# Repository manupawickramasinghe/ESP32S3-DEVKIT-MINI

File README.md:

# ESP32S3-DEVKIT-MINI
 ESP32-S3 DevKIT Made using the Espressif Schematics, Needs more changes and improvements , donot hesitate to make changes and suggest improvements. Final Plan is to implemnt a global datalogger

 It has Mini USB , MIcro USB and TYpe C 

To do:
Implement USB
Add seperate i2c and spi as connectors to connect to modules - Check my datalogger project
Add Silkscreen things -  Need to do
Improve routing and make it prettier

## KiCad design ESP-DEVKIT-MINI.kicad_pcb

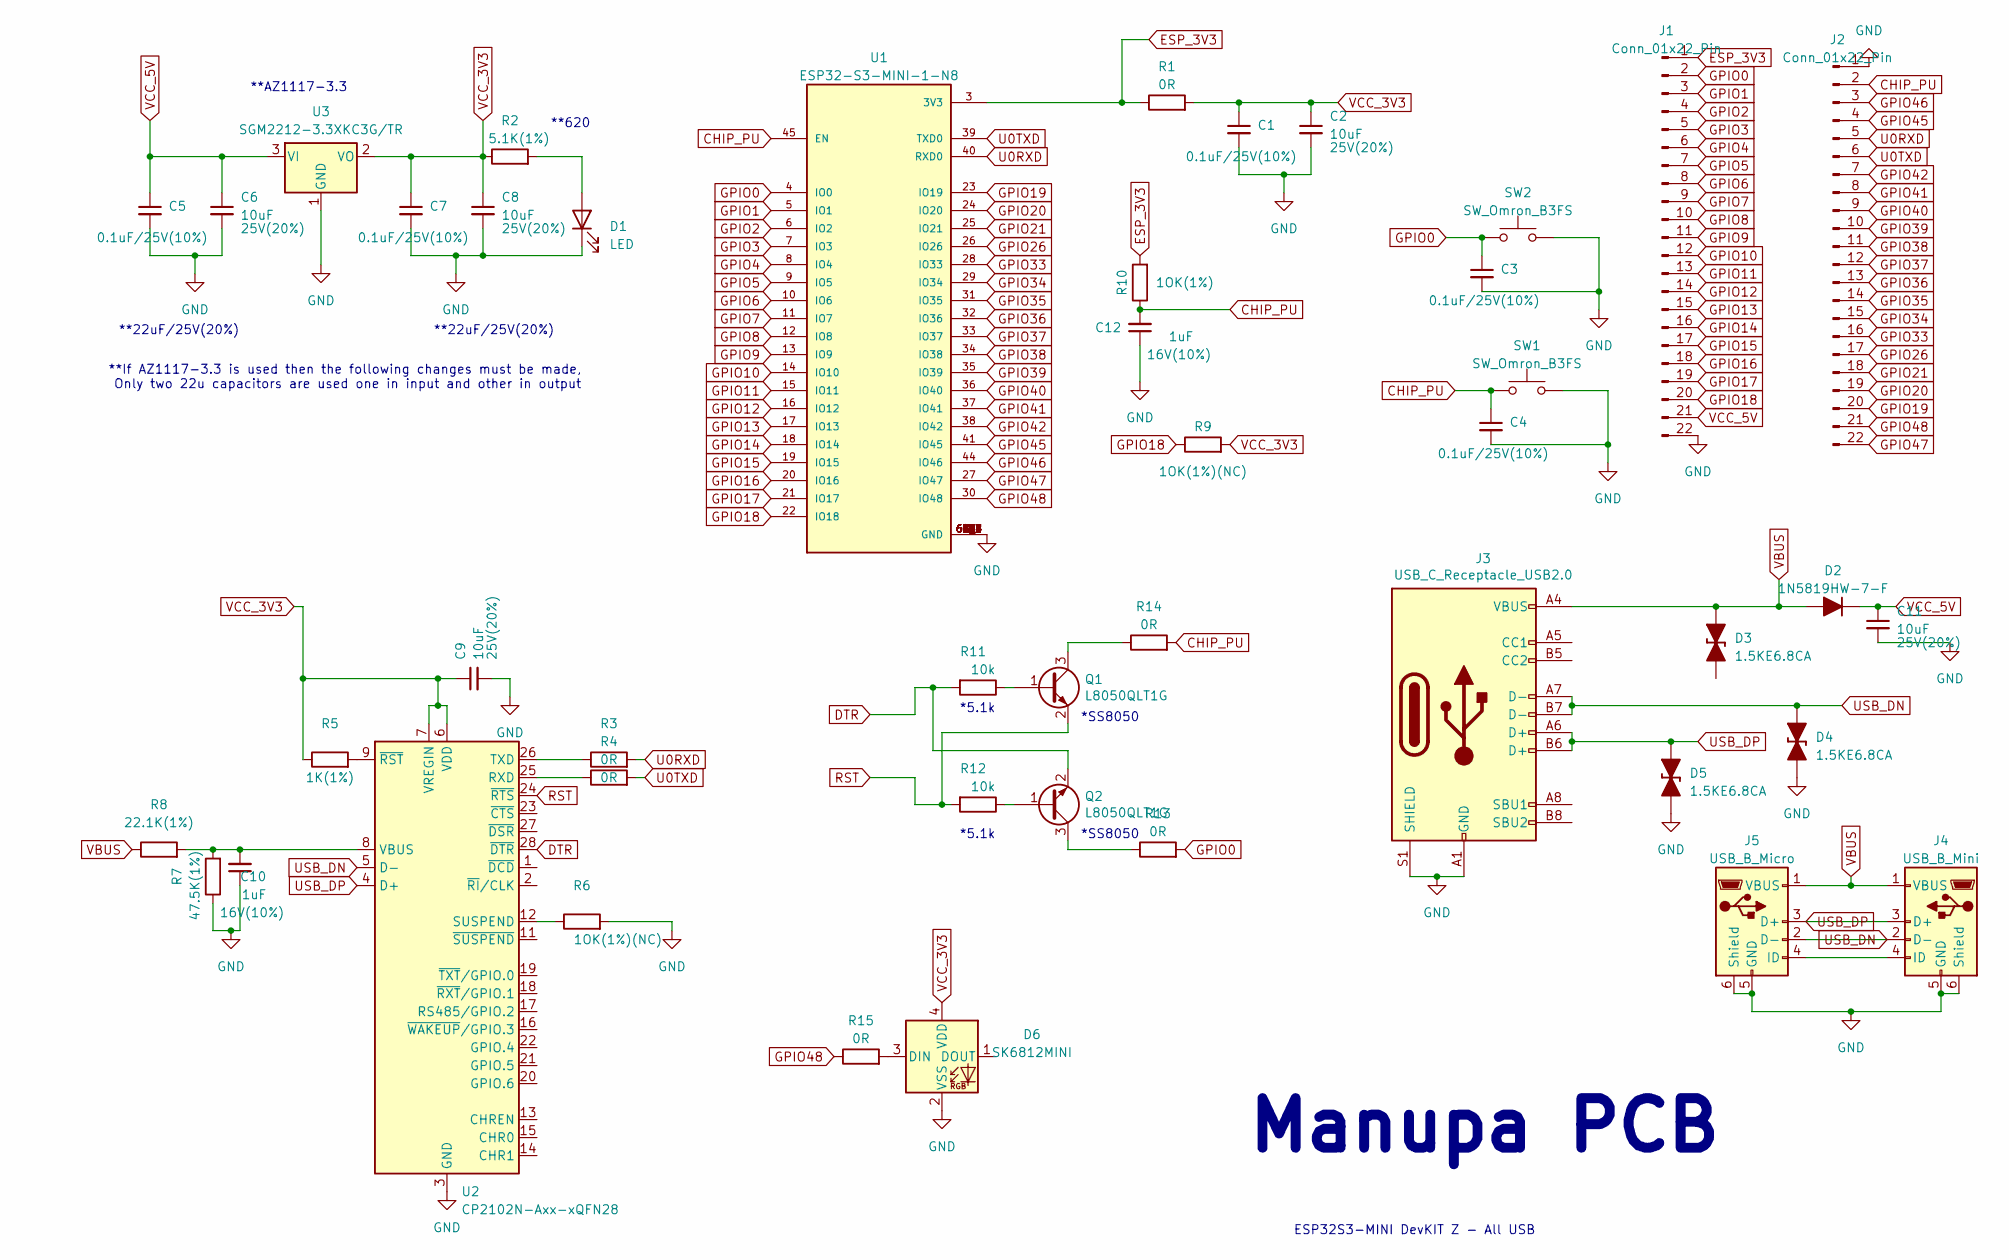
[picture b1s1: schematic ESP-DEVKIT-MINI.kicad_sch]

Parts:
C1, C3, C4, C5, C7: 0.1uF_0603_16V; C_0603_1608Metric; Part Number 0603YC104KAT2A; JLCPCB ID C14663
C2, C6, C8, C9, C11: 10uF_1206_35V; C_0603_1608Metric; Part Number C3216X6S1V106K160AC; JLCPCB ID 25V(20%)
C10, C12: 10uF_1206_35V; C_0603_1608Metric; Part Number C3216X6S1V106K160AC; JLCPCB ID 16V(10%)
D1: LED; LED_0603_1608Metric
D2: 1N5819HW-7-F; D_DO-41_SOD81_P7.62mm_Horizontal
D3, D4, D5: 1.5KE6.8CA; D_DO-201_P12.70mm_Horizontal_TVS
D6: SK6812MINI; LED_SK6812MINI_PLCC4_3.5x3.5mm_P1.75mm
J1, J2: Conn_01x22_Pin; PinHeader_1x22_P2.00mm_Vertical
J3: USB_C_Receptacle_USB2.0; USB_C_Receptacle_Palconn_UTC16-G; LCSC C167321
J4: USB_B_Mini; USB_Mini-B_Lumberg_2486_01_Horizontal
J5: USB_B_Micro; USB_Micro-AB_Molex_47590-0001
Q1, Q2: L8050QLT1G; SOT-23; LCSC C2150
R1, R2, R3, R4, R5, R6, R7, R8, R9, R10, R13, R14, R15: 0R_0603; R_0603; Part Number RC0603FR-100RL; JLCPCB ID C21189
R11, R12: 10k; R_0603; LCSC C25905
SW1, SW2: SW_Omron_B3FS; SW_SPST_Omron_B3FS-100xP
U1: ESP32-S3-MINI-1-N8; XCVR_ESP32-S3-MINI-1-N8; PARTREV v0.6
U2: CP2102N-Axx-xQFN28; QFN-28-1EP_5x5mm_P0.5mm_EP3.35x3.35mm
U3: SGM2212-3.3XKC3G/TR; SOT-223-3_TabPin2

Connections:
CHIP_PU: C4.1, C12.2, J2.2, R10.1, R14.2, SW1.1, U1.45 (EN)
DTR: Q2.2 (E), R11.2, U2.28 (~DTR)
ESP_3V3: J1.1, R1.1, R10.2, U1.3 (3V3)
GND: C1.2, C2.2, C3.2, C4.2, C5.2, C6.2, C7.2, C8.2, C9.2, C10.1, C11.2, C12.1, D1.1 (K), D3.1 (K), D4.1 (K), D5.1 (K), D6.2 (VSS), J1.22, J2.1, J3.A1 (GND), J3.A12 (GND), J3.B1 (GND), J3.B12 (GND), J3.S1 (SHIELD), J4.5 (GND), J4.6 (Shield), J5.5 (GND), J5.6 (Shield), R6.2, R7.1, SW1.2, SW2.2, U1.1 (GND), U1.2 (GND), U1.42 (GND), U1.43 (GND), U1.46 (GND), U1.47 (GND), U1.48 (GND), U1.49 (GND), U1.50 (GND), U1.51 (GND), U1.52 (GND), U1.53 (GND), U1.54 (GND), U1.55 (GND), U1.56 (GND), U1.57 (GND), U1.58 (GND), U1.59 (GND), U1.60 (GND), U1.61 (GND), U1.61_1 (GND), U1.61_2 (GND), U1.61_3 (GND), U1.61_4 (GND), U1.61_5 (GND), U1.61_6 (GND), U1.61_7 (GND), U1.61_8 (GND), U1.62 (GND), U1.63 (GND), U1.64 (GND), U1.65 (GND), U2.3 (GND), U2.29 (GND), U3.1 (GND)
GPIO0: C3.1, J1.2, R13.2, SW2.1, U1.4 (IO0)
GPIO1: J1.3, U1.5 (IO1)
GPIO2: J1.4, U1.6 (IO2)
GPIO3: J1.5, U1.7 (IO3)
GPIO4: J1.6, U1.8 (IO4)
GPIO5: J1.7, U1.9 (IO5)
GPIO6: J1.8, U1.10 (IO6)
GPIO7: J1.9, U1.11 (IO7)
GPIO8: J1.10, U1.12 (IO8)
GPIO9: J1.11, U1.13 (IO9)
GPIO10: J1.12, U1.14 (IO10)
GPIO11: J1.13, U1.15 (IO11)
GPIO12: J1.14, U1.16 (IO12)
GPIO13: J1.15, U1.17 (IO13)
GPIO14: J1.16, U1.18 (IO14)
GPIO15: J1.17, U1.19 (IO15)
GPIO16: J1.18, U1.20 (IO16)
GPIO17: J1.19, U1.21 (IO17)
GPIO18: J1.20, R9.1, U1.22 (IO18)
GPIO19: J2.20, U1.23 (IO19)
GPIO20: J2.19, U1.24 (IO20)
GPIO21: J2.18, U1.25 (IO21)
GPIO26: J2.17, U1.26 (IO26)
GPIO33: J2.16, U1.28 (IO33)
GPIO34: J2.15, U1.29 (IO34)
GPIO35: J2.14, U1.31 (IO35)
GPIO36: J2.13, U1.32 (IO36)
GPIO37: J2.12, U1.33 (IO37)
GPIO38: J2.11, U1.34 (IO38)
GPIO39: J2.10, U1.35 (IO39)
GPIO40: J2.9, U1.36 (IO40)
GPIO41: J2.8, U1.37 (IO41)
GPIO42: J2.7, U1.38 (IO42)
GPIO45: J2.4, U1.41 (IO45)
GPIO46: J2.3, U1.44 (IO46)
GPIO47: J2.22, U1.27 (IO47)
GPIO48: J2.21, R15.1, U1.30 (IO48)
unnamed: D1.2 (A), R2.2
unnamed: D6.3 (DIN), R15.2
unnamed: J4.4 (ID), J5.4 (ID)
unnamed: Q1.1 (B), R11.1
unnamed: Q1.3 (C), R14.1
unnamed: Q2.1 (B), R12.1
unnamed: Q2.3 (C), R13.1
unnamed: R4.1, U2.25 (RXD)
unnamed: R6.1, U2.12 (SUSPEND)
unnamed: R3.1, U2.26 (TXD)
unnamed: C10.2, R7.2, R8.2, U2.8 (VBUS)
unnamed: R5.2, U2.9 (~RST)
RST: Q1.2 (E), R12.2, U2.24 (~RTS)
U0RXD: J2.5, R3.2, U1.40 (RXD0)
U0TXD: J2.6, R4.2, U1.39 (TXD0)
USB_DN: D4.2 (A), J3.A7 (D-), J3.B7 (D-), J4.2 (D-), J5.2 (D-), U2.5 (D-)
USB_DP: D5.2 (A), J3.A6 (D+), J3.B6 (D+), J4.3 (D+), J5.3 (D+), U2.4 (D+)
VBUS: D2.2 (A), D3.2 (A), J3.A4 (VBUS), J3.A9 (VBUS), J3.B4 (VBUS), J3.B9 (VBUS), J4.1 (VBUS), J5.1 (VBUS), R8.1
VCC_3V3: C1.1, C2.1, C7.1, C8.1, C9.1, D6.4 (VDD), R1.2, R2.1, R5.1, R9.2, U2.6 (VDD), U2.7 (VREGIN), U3.2 (VO)
VCC_5V: C5.1, C6.1, C11.1, D2.1 (K), J1.21, U3.3 (VI)

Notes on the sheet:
*SS8050
**If AZ1117-3.3 is used then the following changes must be made, Only two 22u capacitors are used one in input and other in output
**620
**AZ1117-3.3
*5.1k
**22uF/25V(20%)
Manupa PCB
ESP32S3-MINI DevKIT Z - All USB

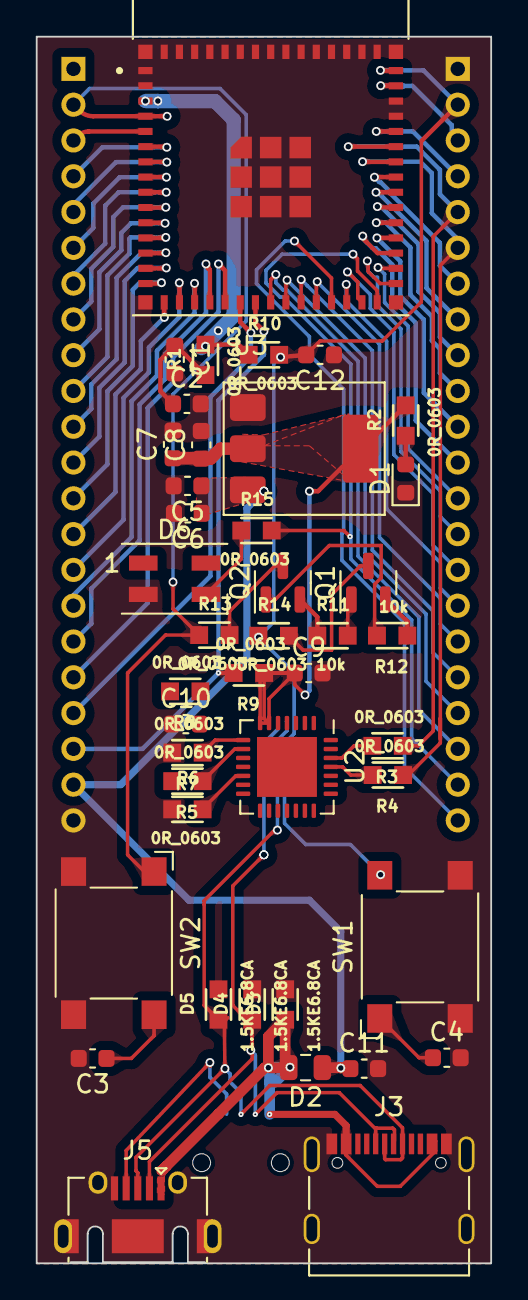
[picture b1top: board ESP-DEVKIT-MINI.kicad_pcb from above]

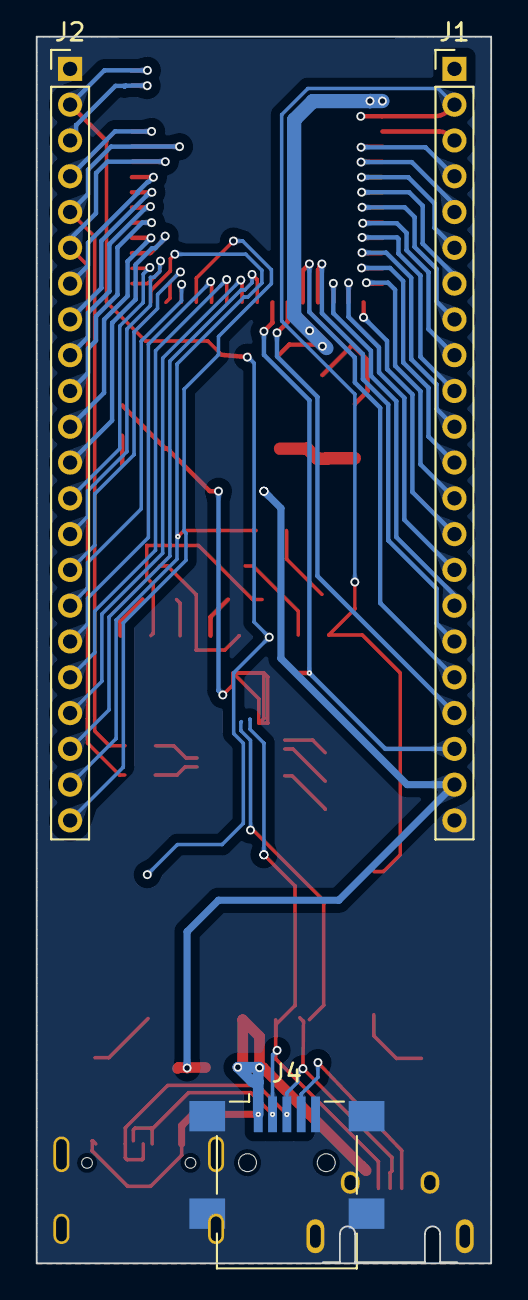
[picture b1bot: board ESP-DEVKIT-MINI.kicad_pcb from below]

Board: 2 copper layers, 25.4 x 68.6 mm, 45 parts (3 on the bottom side), 61 nets.

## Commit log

2023-07-17 Final 1.0
    The PCB routing is finished, and the Silscreen is only to be changed.
    For the BOM the schematic must be used due to the reuse of similar components
2023-07-17 Done
2023-07-20 First DEV Commit
2023-09-24 Code
2023-09-24 Code For ESP32S3
2023-09-24 Major Changes
